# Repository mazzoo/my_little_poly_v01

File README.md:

my_little_poly_v01

1S LiPo with protection to 5V USB converter

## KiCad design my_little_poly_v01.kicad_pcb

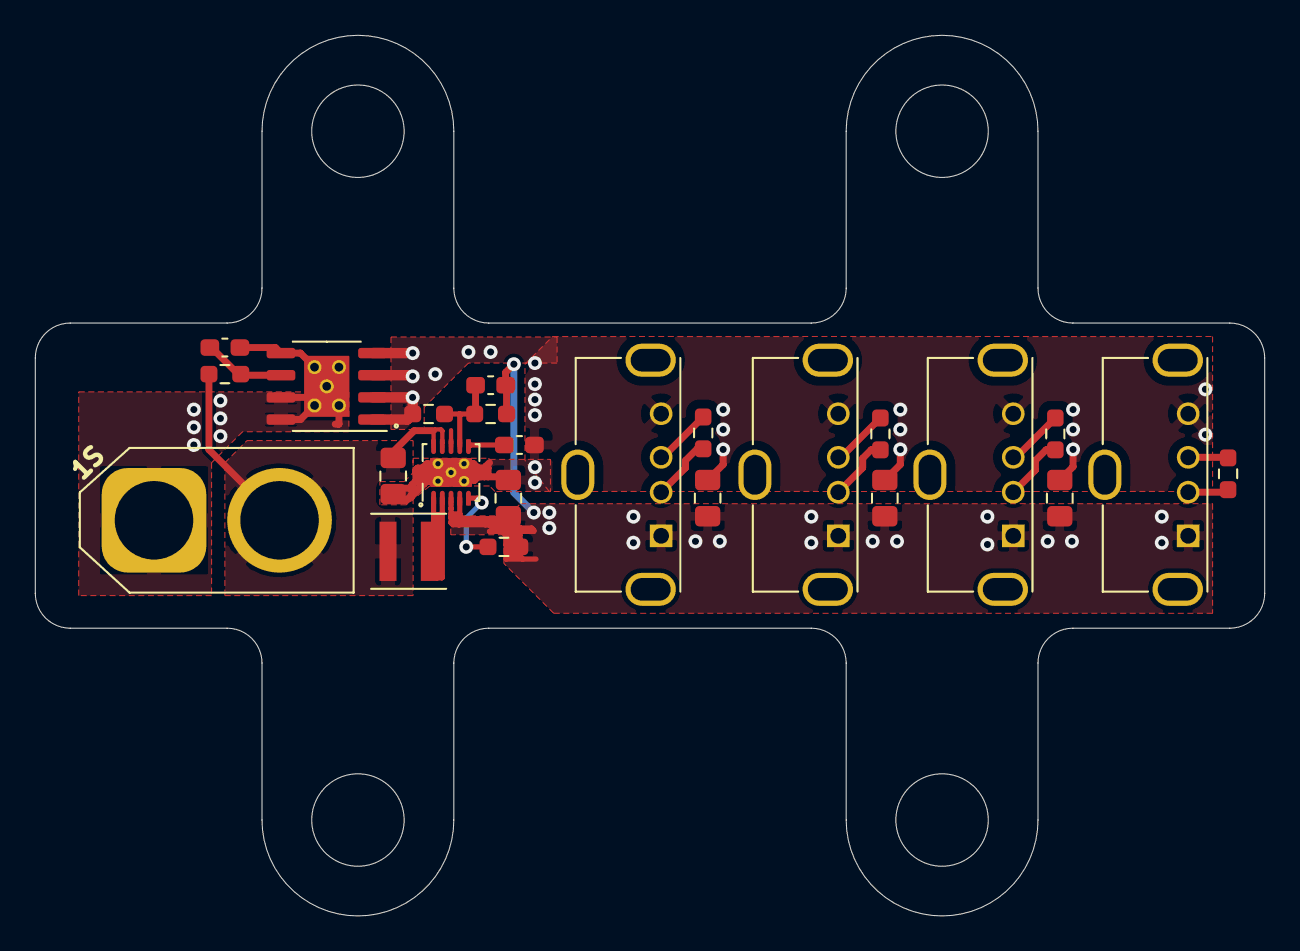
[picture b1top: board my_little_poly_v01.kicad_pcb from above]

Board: 2 copper layers, 70.5 x 50.5 mm, 28 parts (0 on the bottom side), 17 nets.

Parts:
C101, C102, C103, C104, C107: 22uF; C_0805_2012Metric_Pad1.18x1.45mm_HandSolder
C105: 10nF; C_0603_1608Metric_Pad1.08x0.95mm_HandSolder
C106: 18pF; C_0603_1608Metric_Pad1.08x0.95mm_HandSolder
C108: 100n; C_0603_1608Metric_Pad1.08x0.95mm_HandSolder
H101, H102, H103, H104: MountingHole; MountingHole_5.3mm_M5_ISO14580
J101: Conn_01x02_Male; AMASS_XT60-M_1x02_P7.20mm_Vertical
J102, J103, J104, J105: Conn_01x04; USB_A_Molex_105057_Vertical
L101: 1uH; L_Coilcraft_XxL4020
R101: 402k; R_0603_1608Metric_Pad0.98x0.95mm_HandSolder
R102: 100k; R_0603_1608Metric_Pad0.98x0.95mm_HandSolder
R103: 1M; R_0603_1608Metric_Pad0.98x0.95mm_HandSolder
R104: 1k; R_0603_1608Metric_Pad0.98x0.95mm_HandSolder
R105, R106, R107, R108: 0R; R_0603_1608Metric_Pad0.98x0.95mm_HandSolder
U101: TPS61230DRC; Texas_S-PVSON-N10_ThermalVias
U102: XB8089D; SOP-8_3.9x4.9mm_P1.27mm_EP3.5x2.6mm

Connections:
/Bat_minus: C108.2, J101.1, U102.5, U102.7, U102.8, U102.9
/SW: L101.2, U101.1, U101.2
/Vin: C101.1, J101.2, L101.1, R104.2, U101.9, U101.10
/Vout: C102.1, C103.1, C104.1, C106.1, C107.1, J102.1, J103.1, J104.1, J105.1, R101.1, R103.1, U101.3, U101.4
GND: C101.2, C102.2, C103.2, C104.2, C105.2, C107.2, J102.4, J103.4, J104.4, J105.4, R102.2, U101.11, U102.1, U102.2, U102.3, U102.4
unnamed: C105.1, U101.6
unnamed: C106.2, R101.2, R102.1, U101.7
unnamed: C108.1, R104.1, U102.6
unnamed: J102.2, R105.1
unnamed: J102.3, R105.2
unnamed: J103.2, R106.1
unnamed: J103.3, R106.2
unnamed: J104.2, R107.1
unnamed: J104.3, R107.2
unnamed: J105.2, R108.1
unnamed: J105.3, R108.2
unnamed: R103.2, U101.5

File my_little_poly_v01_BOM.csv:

Designator,Quantity,Value,Footprint,LCSC Part #
"C101, C102, C103, C104, C107, ",5,22uF,805,C45783
"C105, ",1,10nF,603,C57112
"C106, ",1,18pF,603,C1647
"C108, ",1,100n,603,C14663
"L101, ",1,1uH,4.0*4.6*2.0,C408332
"R101, ",1,402k,603, C23048
"R102, ",1,100k,603,C25803
"R103, ",1,1M,603, C22935
"R104, ",1,1k,603,C21190
"R105, R106, R107, R108, ",4,0R,603,C21189
"U101, ",1,TPS61230DRC,S-PVSON-N10_ThermalVias,C139626
"U102, ",1,XB8089D,SOP-8_3.9x4.9mm_P1.27mm_EP3.5x2.6mm,C79928

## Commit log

2021-08-20 add readme
